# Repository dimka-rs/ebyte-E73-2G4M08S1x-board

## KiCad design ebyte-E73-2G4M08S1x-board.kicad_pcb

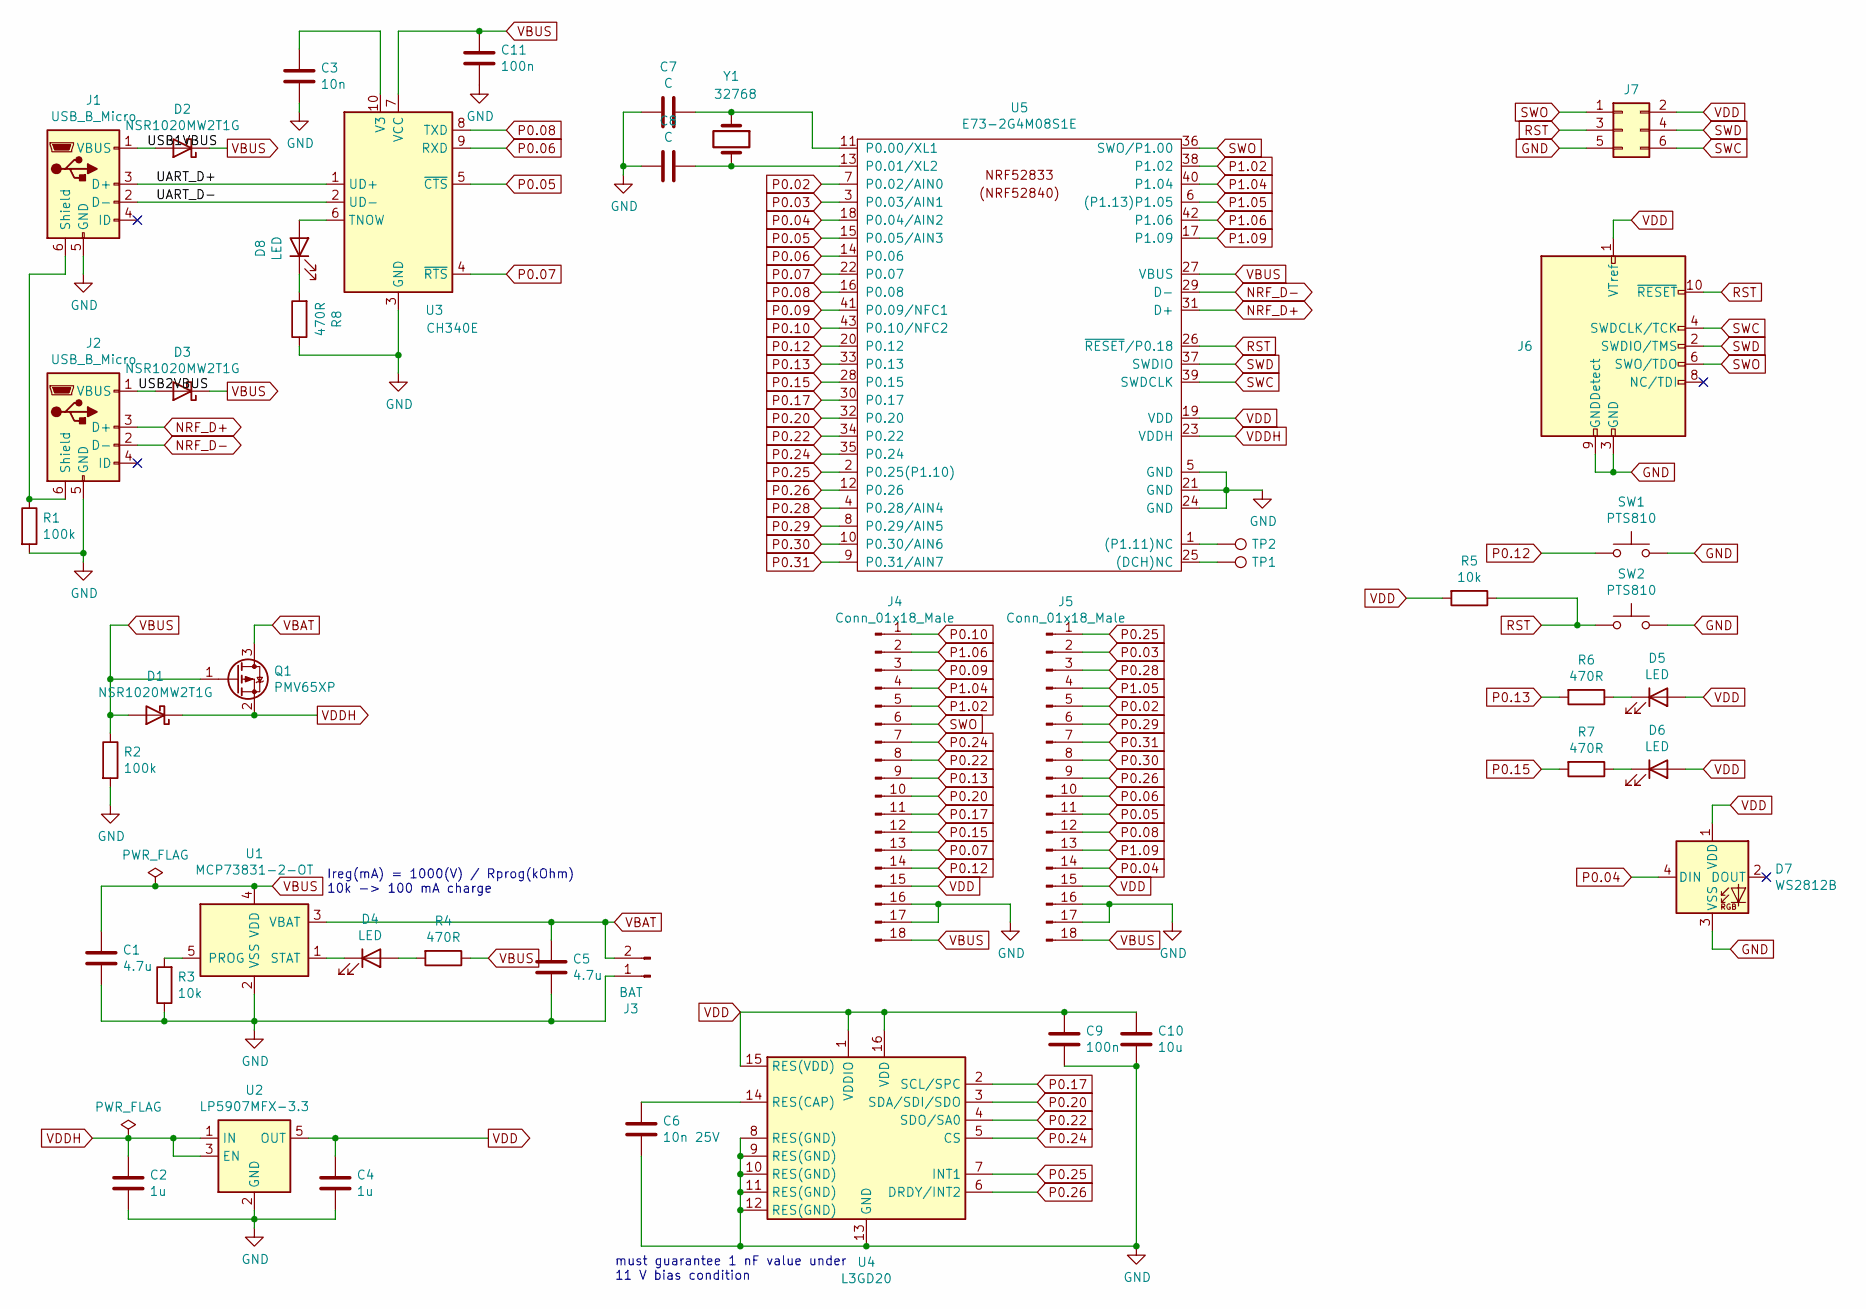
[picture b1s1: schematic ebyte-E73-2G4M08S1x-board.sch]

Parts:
C1, C5: 4.7u; C_0603_1608Metric
C2, C4: 1u; C_0603_1608Metric
C3: 10n; C_0603_1608Metric
C6: 10n 25V; C_0603_1608Metric
C7, C8: C; C_0603_1608Metric
C9, C11: 100n; C_0603_1608Metric
C10: 10u; C_0603_1608Metric
D1, D2, D3: NSR1020MW2T1G; D_SOD-323
D4, D5, D6, D8: LED; LED_0603_1608Metric
D7: WS2812B; LED_WS2812B_PLCC4_5.0x5.0mm_P3.2mm
J1, J2: USB_B_Micro; USB_Micro-B_Amphenol_10103594-0001LF_Horizontal
J3: BAT; PinHeader_1x02_P2.54mm_Vertical
J4, J5: Conn_01x18_Male; PinHeader_1x18_P2.54mm_Vertical
J6: Conn_ARM_JTAG_SWD_10; PinHeader_2x05_P1.27mm_Vertical_SMD
J7: Conn_02x03_Odd_Even; PinHeader_2x03_P2.54mm_Vertical
Q1: PMV65XP; SOT-23
R1, R2: 100k; R_0603_1608Metric
R3, R5: 10k; R_0603_1608Metric
R4, R6, R7, R8: 470R; R_0603_1608Metric
SW1, SW2: PTS810; SW_SPST_PTS810
TP1, TP2: TestPoint; TestPoint_Pad_1.0x1.0mm
U1: MCP73831-2-OT; SOT-23-5
U2: LP5907MFX-3.3; SOT-23-5
U3: CH340E; MSOP-10_3x3mm_P0.5mm
U4: L3GD20; LGA-16_4x4mm_P0.65mm_LayoutBorder4x4y
U5: E73-2G4M08S1E; ebyte-E73-2G4M08S1x
Y1: 32768; Crystal_SMD_MicroCrystal_MS3V-T1R

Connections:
/UART_D+: J1.3 (D+), U3.1 (UD+)
/UART_D-: J1.2 (D-), U3.2 (UD-)
/USB1VBUS: D2.2 (A), J1.1 (VBUS)
/USB2VBUS: D3.2 (A), J2.1 (VBUS)
GND: C1.2, C2.2, C3.1, C4.2, C5.2, C6.2, C7.2, C8.2, C9.2, C10.2, C11.1, D7.3 (VSS), J1.5 (GND), J2.5 (GND), J3.1, J4.16, J4.17, J5.16, J5.17, J6.3 (GND), J6.5 (GND), J6.9 (GNDDetect), J7.5, R1.2, R2.2, R3.1, R8.1, SW1.2, SW2.2, U1.2 (VSS), U2.2 (GND), U3.3 (GND), U4.8 (RES(GND)), U4.9 (RES(GND)), U4.10 (RES(GND)), U4.11 (RES(GND)), U4.12 (RES(GND)), U4.13 (GND), U5.5 (GND), U5.21 (GND), U5.24 (GND)
NRF_D+: J2.3 (D+), U5.31 (D+)
NRF_D-: J2.2 (D-), U5.29 (D-)
unnamed: C3.2, U3.10 (V3)
unnamed: C6.1, U4.14 (RES(CAP))
unnamed: C7.1, U5.11 (P0.00/XL1), Y1.1
unnamed: C8.1, U5.13 (P0.01/XL2), Y1.2
unnamed: D4.1 (K), U1.1 (STAT)
unnamed: D4.2 (A), R4.2
unnamed: D5.1 (K), R6.1
unnamed: D6.1 (K), R7.1
unnamed: D8.1 (K), R8.2
unnamed: D8.2 (A), U3.6 (TNOW)
unnamed: J1.6 (Shield), J2.6 (Shield), R1.1
unnamed: R3.2, U1.5 (PROG)
unnamed: TP1.1, U5.25 ((DCH)NC)
unnamed: TP2.1, U5.1 ((P1.11)NC)
P0.02: J5.5, U5.7 (P0.02/AIN0)
P0.03: J5.2, U5.3 (P0.03/AIN1)
P0.04: D7.4 (DIN), J5.14, U5.18 (P0.04/AIN2)
P0.05: J5.11, U3.5 (~CTS), U5.15 (P0.05/AIN3)
P0.06: J5.10, U3.9 (RXD), U5.14 (P0.06)
P0.07: J4.13, U3.4 (~RTS), U5.22 (P0.07)
P0.08: J5.12, U3.8 (TXD), U5.16 (P0.08)
P0.09: J4.3, U5.41 (P0.09/NFC1)
P0.10: J4.1, U5.43 (P0.10/NFC2)
P0.12: J4.14, SW1.1, U5.20 (P0.12)
P0.13: J4.9, R6.2, U5.33 (P0.13)
P0.15: J4.12, R7.2, U5.28 (P0.15)
P0.17: J4.11, U4.2 (SCL/SPC), U5.30 (P0.17)
P0.20: J4.10, U4.3 (SDA/SDI/SDO), U5.32 (P0.20)
P0.22: J4.8, U4.4 (SDO/SA0), U5.34 (P0.22)
P0.24: J4.7, U4.5 (CS), U5.35 (P0.24)
P0.25: J5.1, U4.7 (INT1), U5.2 (P0.25(P1.10))
P0.26: J5.9, U4.6 (DRDY/INT2), U5.12 (P0.26)
P0.28: J5.3, U5.4 (P0.28/AIN4)
P0.29: J5.6, U5.8 (P0.29/AIN5)
P0.30: J5.8, U5.10 (P0.30/AIN6)
P0.31: J5.7, U5.9 (P0.31/AIN7)
P1.02: J4.5, U5.38 (P1.02)
P1.04: J4.4, U5.40 (P1.04)
P1.05: J5.4, U5.6 ((P1.13)P1.05)
P1.06: J4.2, U5.42 (P1.06)
P1.09: J5.13, U5.17 (P1.09)
RST: J6.10 (~RESET~), J7.3, R5.1, SW2.1, U5.26 (~RESET~/P0.18)
SWC: J6.4 (SWDCLK/TCK), J7.6, U5.39 (SWDCLK)
SWD: J6.2 (SWDIO/TMS), J7.4, U5.37 (SWDIO)
SWO: J4.6, J6.6 (SWO/TDO), J7.1, U5.36 (SWO/P1.00)
VBAT: C5.1, J3.2, Q1.3 (D), U1.3 (VBAT)
VBUS: C1.1, C11.2, D1.2 (A), D2.1 (K), D3.1 (K), J4.18, J5.18, Q1.1 (G), R2.1, R4.1, U1.4 (VDD), U3.7 (VCC), U5.27 (VBUS)
VDD: C4.1, C9.1, C10.1, D5.2 (A), D6.2 (A), D7.1 (VDD), J4.15, J5.15, J6.1 (VTref), J7.2, R5.2, U2.5 (OUT), U4.1 (VDDIO), U4.15 (RES(VDD)), U4.16 (VDD), U5.19 (VDD)
VDDH: C2.1, D1.1 (K), Q1.2 (S), U2.1 (IN), U2.3 (EN), U5.23 (VDDH)

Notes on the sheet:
Ireg(mA) = 1000(V) / Rprog(kOhm) 10k -> 100 mA charge
must guarantee 1 nF value under 11 V bias condition

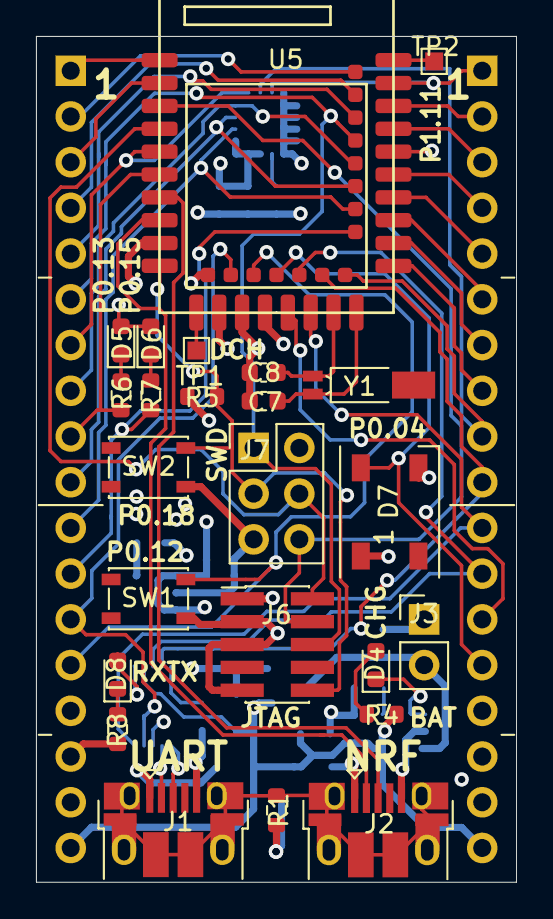
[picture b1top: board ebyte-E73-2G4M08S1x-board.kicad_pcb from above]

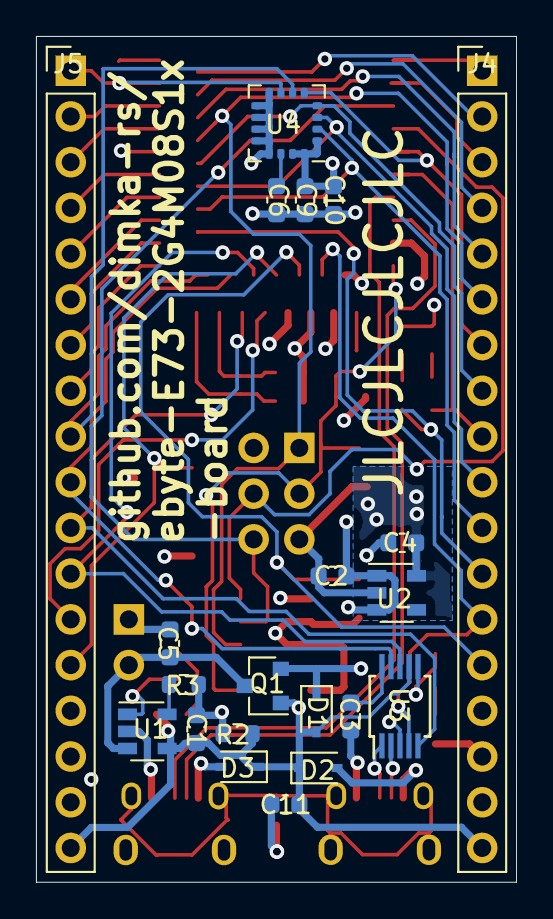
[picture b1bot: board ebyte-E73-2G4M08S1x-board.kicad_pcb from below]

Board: 4 copper layers, 26.7 x 47.0 mm, 45 parts (21 on the bottom side), 56 nets.

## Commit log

2021-03-10 Initial
2021-03-11 Preliminary PCB layout
2021-05-29 Update sch, pcb, bom
2021-05-30 Improve silk
2021-05-30 Add gerbers
2021-05-30 Add readme and renders
2021-06-03 Fix module footprint, rework PCB
2021-06-05 Update BOM and images
2021-06-05 Fix bottom render
2021-06-05 Update gerbers
